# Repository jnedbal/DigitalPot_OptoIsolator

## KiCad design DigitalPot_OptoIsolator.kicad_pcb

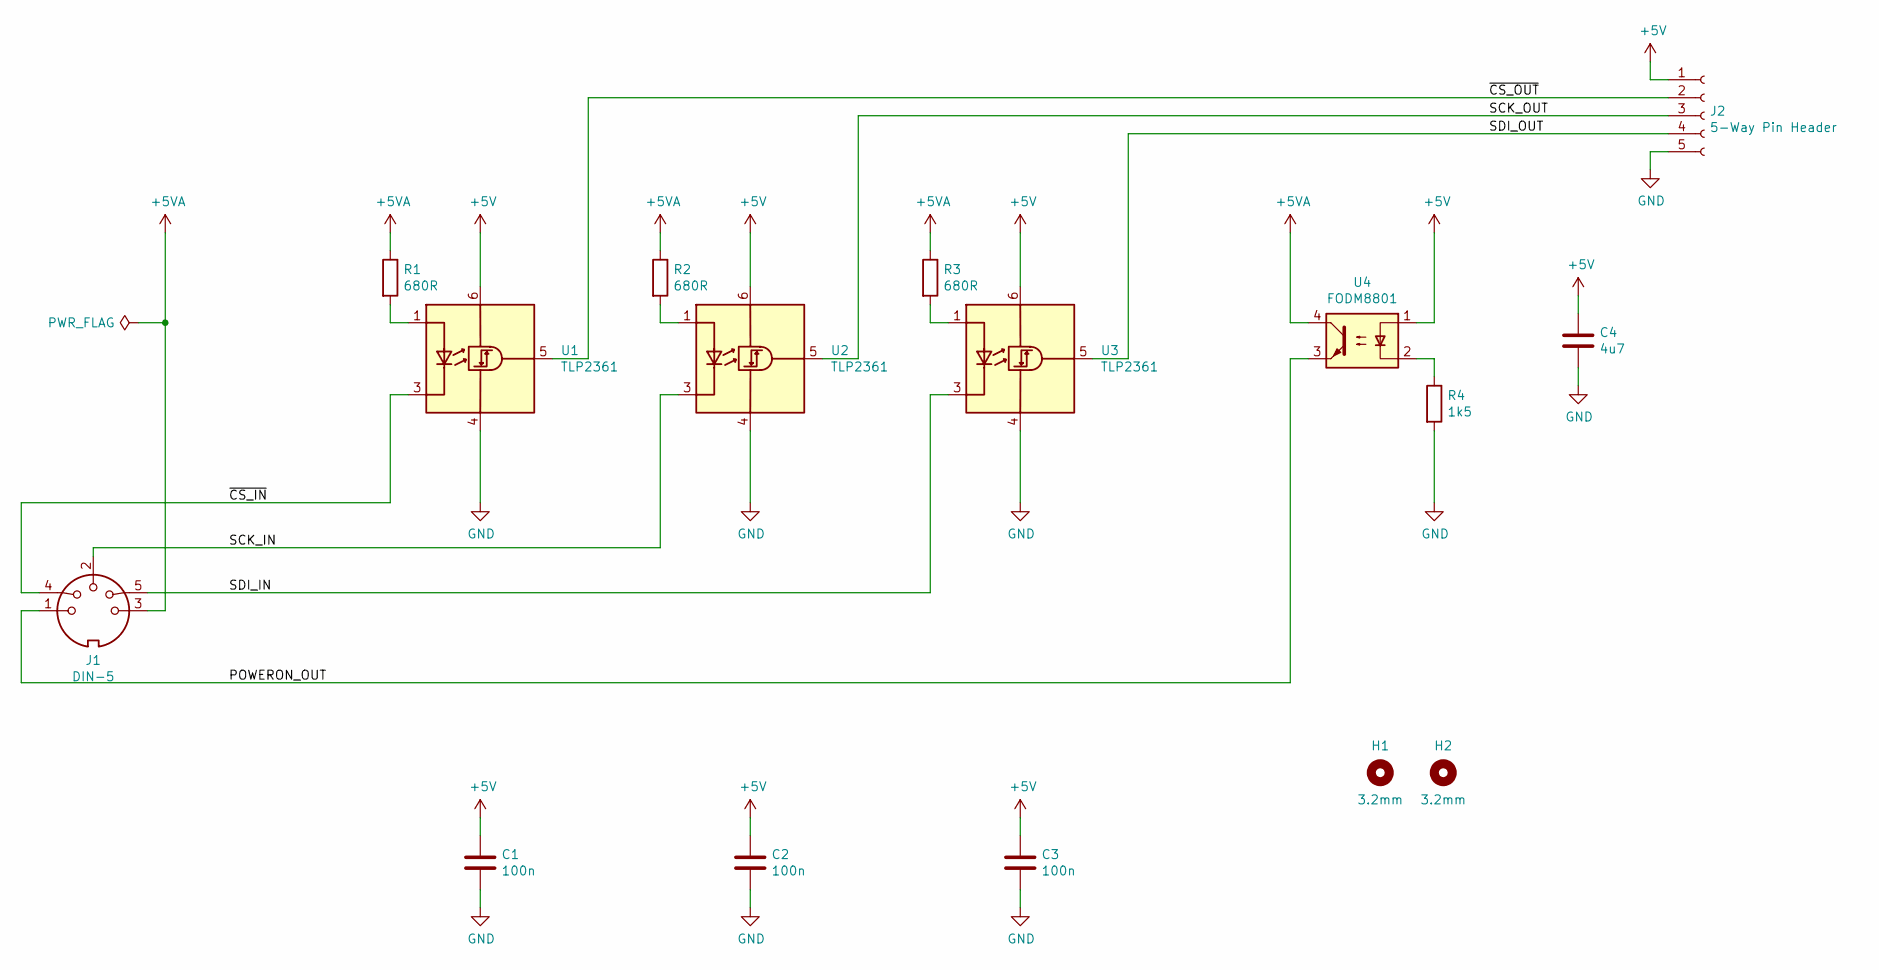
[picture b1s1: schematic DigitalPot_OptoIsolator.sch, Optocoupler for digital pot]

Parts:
C1, C2, C3: 100n; C_0603_1608Metric; Part Number MC0603B104K500
C4: 4u7; C_0603_1608Metric; Part Number EMK107ABJ475KA-T
H1, H2: 3.2mm; MountingHole_3.2mm_M3
J1: DIN-5; DIN5; Part Number MAB 5 SV
J2: 5-Way Pin Header; PinHeader_1x05_P2.54mm_Vertical; Part Number 2211S-05G
R1, R2, R3: 680R; R_0603_1608Metric; Part Number MCWR06X6800FTL
R4: 1k5; R_0603_1608Metric; Part Number MCWR06X1501FTL
U1, U2, U3: TLP2361; SO-6_4.4x3.6mm_P1.27mm; Part Number TLP2361
U4: FODM8801; SO-4_4.4x2.3mm_P1.27mm; Part Number FODM8801CR2

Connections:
+5V: C1.1, C2.1, C3.1, C4.1, J2.1, U1.6 (VDD), U2.6 (VDD), U3.6 (VDD), U4.1
+5VA: J1.3, R1.1, R2.1, R3.1, U4.4
/POWERON_OUT: J1.1, U4.3
/SCK_IN: J1.2, U2.3 (K)
/SCK_OUT: J2.3, U2.5 (VO)
/SDI_IN: J1.5, U3.3 (K)
/SDI_OUT: J2.4, U3.5 (VO)
/~CS_IN: J1.4, U1.3 (K)
/~CS_OUT: J2.2, U1.5 (VO)
GND: C1.2, C2.2, C3.2, C4.2, J2.5, R4.2, U1.4 (GND), U2.4 (GND), U3.4 (GND)
unnamed: R1.2, U1.1 (A)
unnamed: R2.2, U2.1 (A)
unnamed: R3.2, U3.1 (A)
unnamed: R4.1, U4.2

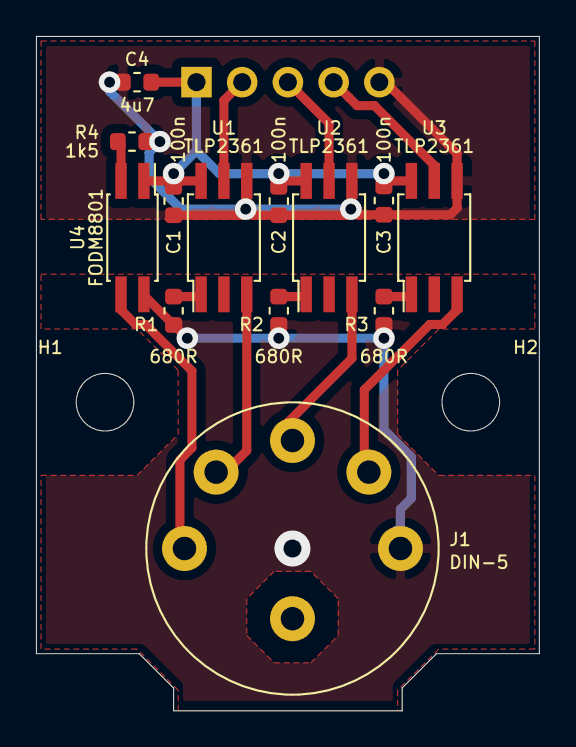
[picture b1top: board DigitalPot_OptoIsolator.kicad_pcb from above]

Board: 2 copper layers, 27.9 x 37.5 mm, 16 parts (1 on the bottom side), 14 nets.

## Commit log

2019-07-19 Sent for manufacture
2019-08-08 Made board smaller to fit the box, removed two mounting screws, made central hole larger diameter so it can be used as a marking hole.
2023-02-03 Tidied up the schematics
2023-02-15 Added the aluminium enclosure to the schematics

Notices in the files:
DigitalPot_OptoIsolator.kicad_pcb:
CC-BY
